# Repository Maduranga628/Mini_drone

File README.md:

This design intended to use coreless motors.

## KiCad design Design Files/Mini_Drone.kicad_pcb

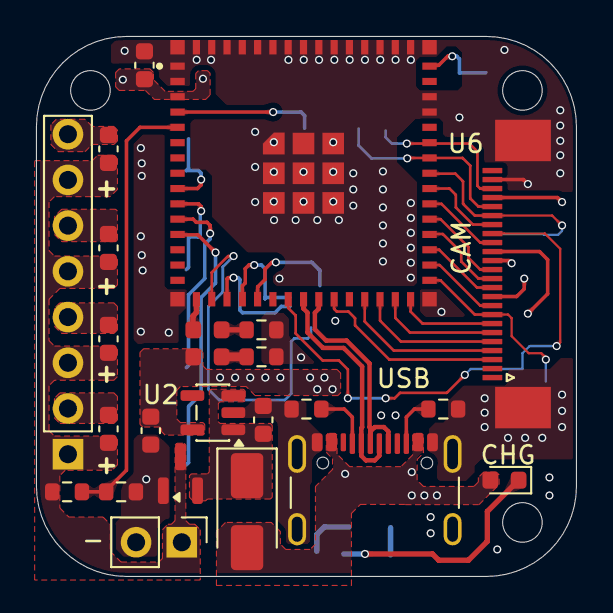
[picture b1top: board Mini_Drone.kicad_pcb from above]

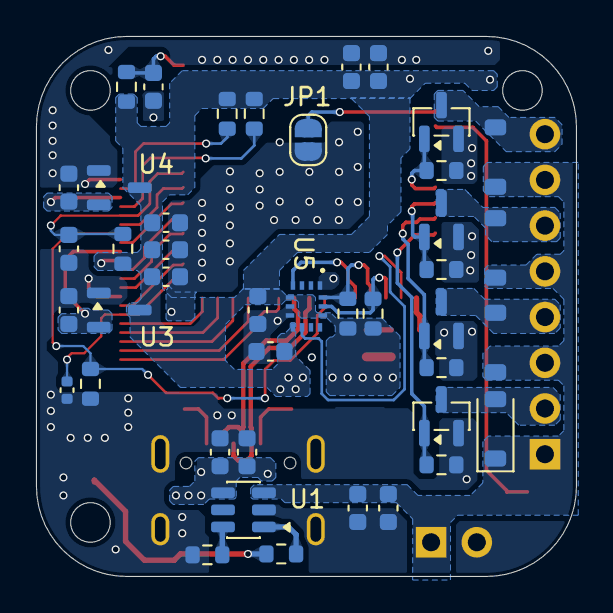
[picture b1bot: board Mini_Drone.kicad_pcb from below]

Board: 4 copper layers, 30.0 x 30.0 mm, 69 parts (42 on the bottom side), 48 nets.

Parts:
-: BAT_Conn; PinHeader_1x02_P2.54mm_Vertical
C1, C2, C3, C4, C5, C6, C7, C8, C9, C10, C11, C12, C13, C14, C22, C23: 1u; C_0603_1608Metric
C15, C16, C18, C19, C20, C21: 100n; C_0603_1608Metric
C17: 15p; C_0402_1005Metric
CAM: FPC_Conn_01x24_Pin; TE_2-1734839-4_1x24-1MP_P0.5mm_Horizontal
CHG: LED; LED_0603_1608Metric
D1, D2, D3, D4: 1N4148W; D_SOD-123
D5: SS24; D_SMA
D8, D11: LED; LED_0603_1608Metric
H5, H6, H7: MountingHole; MountingHole_2.2mm_M2
J5: Conn_01x08_Pin; PinSocket_1x08_P2.54mm_Vertical
JP1: Jumper_2_Small_Open; SolderJumper-2_P1.3mm_Open_RoundedPad1.0x1.5mm
Q1, Q2, Q3, Q4: AO3400A; SOT-23
Q5: AO3401A; SOT-23
R1, R2, R3, R4, R16, R17, R18, R20, R21, R22: 10k; R_0603_1608Metric
R5: 100k; R_0603_1608Metric
R6: 220k; R_0603_1608Metric
R7, R8: 5k1; R_0603_1608Metric
R10, R12, R19: 1k; R_0603_1608Metric
R11: 3k3; R_0603_1608Metric
R15: 330R; R_0603_1608Metric
U1: TP4057; TSOT-23-6
U2: TLV75733PDBV; SOT-23-5
U3: SSP7615-12MR; SOT-23-3
U4: SSP6206-28MR; SOT-23-3
U5: BMI270
U6: ESP32-S3-MINI-1-N8; ESP32-S3-MINI-1
USB: USB_C; USB_C_Receptacle_GCT_USB4105-xx-A_16P_TopMnt_Horizontal

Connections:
+1V2: C12.1, CAM.15, U3.2 (VO)
+2V8: C14.1, CAM.21, U4.2 (VO)
+3V3: C10.1, C11.1, C13.1, C15.1, C18.1, C19.1, C20.1, C21.1, C22.1, CAM.14, D8.2 (A), R16.1, R17.1, R18.1, R20.1, R21.1, R22.1, U2.5 (OUT), U3.3 (VI), U4.3 (VI), U5.5 (VDDIO), U5.8 (VDD), U5.12 (CSB), U6.3 (3V3)
+5V: C9.1, D5.1 (K), Q5.2 (S), U2.1 (IN), U2.3 (EN)
+VBAT: -.1, C1.1, C2.1, C3.1, C4.1, C5.1, C8.1, D1.1 (K), D2.1 (K), D3.1 (K), D4.1 (K), J5.1, J5.3, J5.5, J5.7, Q5.3 (D), R5.1, U1.3 (BAT)
+VBUS: C6.1, C7.1, CHG.2 (A), D5.2 (A), U1.4 (V_{CC}), USB.A4 (VBUS), USB.A9 (VBUS), USB.B4 (VBUS), USB.B9 (VBUS)
/BAT_SENSE: R5.2, R6.1, U6.5 (IO1)
/BOOT_SEL: JP1.2 (B), U6.4 (IO0)
/CAM_SCL: CAM.20, R16.2, U6.39 (TXD0/IO43)
/CAM_SDA: CAM.22, R17.2, U6.40 (RXD0/IO44)
/CHG_PROG: R11.1, U1.6 (PROG)
/DVP_D0: CAM.6, U6.29 (IO34)
/DVP_D1: CAM.4, U6.27 (IO47)
/DVP_D2: CAM.3, U6.25 (IO21)
/DVP_D3: CAM.5, U6.28 (IO33)
/DVP_D4: CAM.7, U6.30 (IO48)
/DVP_D5: CAM.9, U6.32 (IO36)
/DVP_D6: CAM.11, U6.33 (IO37)
/DVP_D7: CAM.13, U6.35 (IO39)
/DVP_HSYNC: CAM.16, U6.36 (IO40)
/DVP_MCLK: CAM.12, U6.34 (IO38)
/DVP_PCLK: C17.1, CAM.8, U6.31 (IO35)
/DVP_RST: C16.1, CAM.19, R18.2, U6.38 (IO42)
/DVP_VSYNC: CAM.18, U6.37 (IO41)
/ESP_EN: C23.1, R22.2, U6.45 (EN)
/IMU_INT1: U5.4 (INT1), U6.20 (IO16)
/IMU_INT2: U5.9 (INT2), U6.17 (IO13)
/IMU_SCL: R21.2, U5.13 (SCX), U6.18 (IO14)
/IMU_SDA: R20.2, U5.14 (SDX), U6.19 (IO15)
/M1_OUT: C1.2, D1.2 (A), J5.2, Q1.3 (D)
/M2_OUT: C2.2, D2.2 (A), J5.4, Q2.3 (D)
/M3_OUT: C3.2, D3.2 (A), J5.6, Q3.3 (D)
/M4_OUT: C4.2, D4.2 (A), J5.8, Q4.3 (D)
/M_1: Q1.1 (G), R1.1, U6.12 (IO8)
/M_2: Q2.1 (G), R2.1, U6.11 (IO7)
/M_3: Q3.1 (G), R3.1, U6.10 (IO6)
/M_4: Q4.1 (G), R4.1, U6.9 (IO5)
/PWR_LEDC: D8.1 (K), R12.1
/STATUS: D11.2 (A), U6.16 (IO12)
/STATUS_LEDC: D11.1 (K), R15.1
/USB_CC1: R8.1, USB.A5 (CC1)
/USB_CC2: R7.1, USB.B5 (CC2)
/USB_D_N: U6.23 (IO19), USB.A7 (D-), USB.B7 (D-)
/USB_D_P: U6.24 (IO20), USB.A6 (D+), USB.B6 (D+)
/~CAM_PW: CAM.17, R19.1, U6.22 (IO18)
/~CHRG: R10.2, U1.1 (~CHRG)
/~CHRG_LEDC: CHG.1 (K), R10.1
GND: -.2, C5.2, C6.2, C7.2, C8.2, C9.2, C10.2, C11.2, C12.2, C13.2, C14.2, C15.2, C16.2, C17.2, C18.2, C19.2, C20.2, C21.2, C22.2, C23.2, CAM.10, CAM.23, CAM.MP (Pad), JP1.1 (A), Q1.2 (S), Q2.2 (S), Q3.2 (S), Q4.2 (S), Q5.1 (G), R1.2, R2.2, R3.2, R4.2, R6.2, R7.2, R8.2, R11.2, R12.2, R15.2, R19.2, U1.2 (GND), U2.2 (GND), U3.1 (GND), U4.1 (GND), U5.1 (SDO), U5.6 (GNDIO), U5.7 (GND), U6.1 (GND), U6.2 (GND__1), U6.42 (GND__2), U6.43 (GND__3), U6.46 (GND__4), U6.47 (GND__5), U6.48 (GND__6), U6.49 (GND__7), U6.50 (GND__8), U6.51 (GND__9), U6.52 (GND__10), U6.53 (GND__11), U6.54 (GND__12), U6.55 (GND__13), U6.56 (GND__14), U6.57 (GND__15), U6.58 (GND__16), U6.59 (GND__17), U6.60 (GND__18), U6.61 (GND__19), U6.61_1 (GND__20), U6.61_2 (GND__21), U6.61_3 (GND__22), U6.61_4 (GND__23), U6.61_5 (GND__24), U6.61_6 (GND__25), U6.61_7 (GND__26), U6.61_8 (GND__27), U6.62 (GND__28), U6.63 (GND__29), U6.64 (GND__30), U6.65 (GND__31), USB.A1 (GND), USB.A12 (GND), USB.B1 (GND), USB.B12 (GND), USB.S1 (SHIELD)

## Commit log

2026-03-18 Create a
